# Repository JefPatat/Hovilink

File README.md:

# Hovilink
**Ho**mebrew **vi**essmann Opto**link** is a serial to network interface built to connect a Viessmann Vitotronic heating control to the network or internet.

# Motivation
I have been using a bulky self built interface based on information available openv together with PC software. This setup was not handy and serious overkill for the purpose. I want to enable myself to communicate with my heater over the network. To keep this flexible the harware is split up in an interface module which translates the optical signals to RS232. This RS232 can then be connected with various other interfaces.

# Limitations
The initial setup of this repository only aims to opensource my personal project and is limited to my personal heater and setup. I'm open to input of the community to expand on this.

# Hardware
The Vitotronic uses an optocoupler to communicate. It uses its status LEDs for this. The left, red, LED functions as an error indicator and at the same time as an infrared receiver. The right, green, LED as an operation indicator an infrared transmitter. Further details will be added to the wiki.

# Software
TBD

# Credits
https://openv.wikispaces.com

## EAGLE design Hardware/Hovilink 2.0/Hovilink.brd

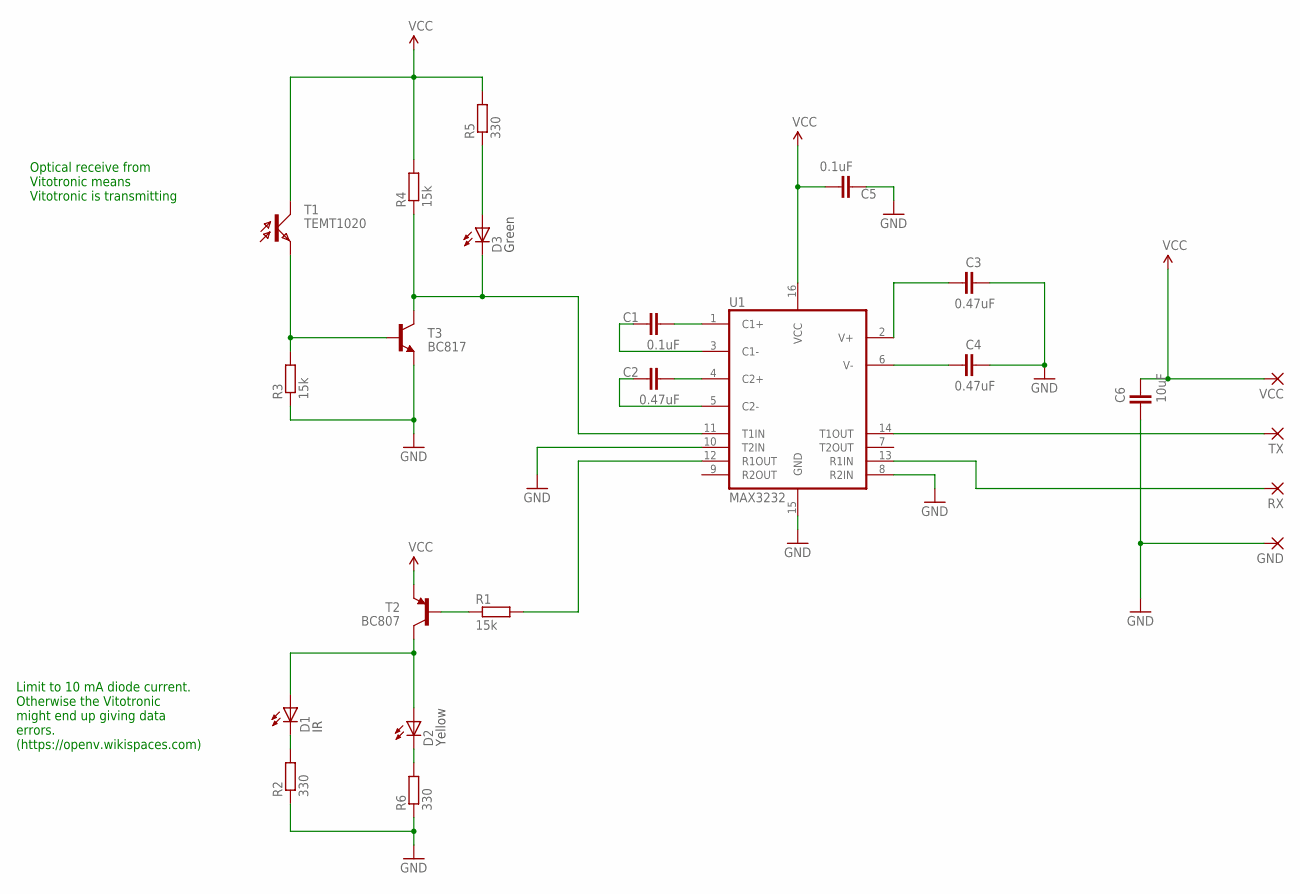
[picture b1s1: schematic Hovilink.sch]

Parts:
C1, C5: 0.1uF; 1206
C2, C3, C4: 0.47uF; 1206
C6: 10uF; 1206
D1: TSMF1020
D2: KP-2012SYCK; KNIGHTBRIGHT_2.0X1.25_SMD_LED
D3: KP-2012CGCK; KNIGHTBRIGHT_2.0X1.25_SMD_LED
GND: WIREPAD_2,54/1,3
R1, R3, R4: 15k; 1206
R2, R5, R6: 330; 1206
RX: WIREPAD_2,54/1,3
T1: TEMT1020
T2: BC807; SOT23_3
T3: BC817; SOT23_3
TX: WIREPAD_2,54/1,3
U1: MAX3232; SOIC16
VCC: WIREPAD_2,54/1,3

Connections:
GND: C3.2, C4.2, C5.1, C6.1, GND.1, R2.1, R3.1, R6.1, T3.2 (E), U1.8 (R2IN), U1.10 (T2IN), U1.15 (GND)
unnamed: C4.1, U1.6 (V-)
unnamed: C3.1, U1.2 (V+)
unnamed: R1.1, T2.1 (B)
unnamed: C1.2, U1.1 (C1+)
unnamed: C1.1, U1.3 (C1-)
unnamed: C2.2, U1.4 (C2+)
unnamed: C2.1, U1.5 (C2-)
unnamed: D1.P$1 (C), R2.2
unnamed: D1.P$2 (A), D2.P$1 (A), T2.3 (C)
unnamed: R1.2, U1.12 (R1OUT)
unnamed: TX.1, U1.14 (T1OUT)
unnamed: RX.1, U1.13 (R1IN)
unnamed: R3.2, T1.P$2 (E), T3.1 (B)
unnamed: D3.P$2 (C), R4.1, T3.3 (C), U1.11 (T1IN)
unnamed: D2.P$2 (C), R6.2
unnamed: D3.P$1 (A), R5.1
VCC: C5.2, C6.2, R4.2, R5.2, T1.P$1 (C), T2.2 (E), U1.16 (VCC), VCC.1

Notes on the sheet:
Optical receive from Vitotronic means Vitotronic is transmitting
Limit to 10 mA diode current. Otherwise the Vitotronic might end up giving data errors. (https://openv.wikispaces.com)

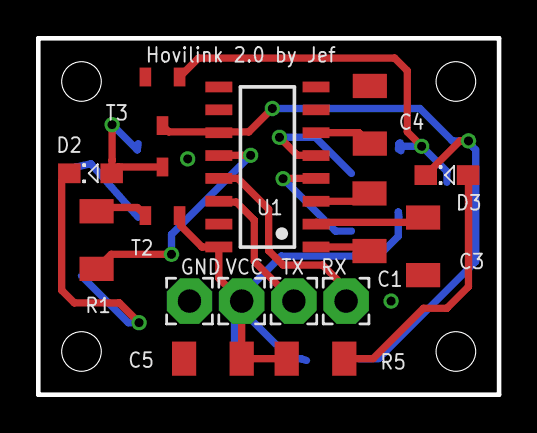
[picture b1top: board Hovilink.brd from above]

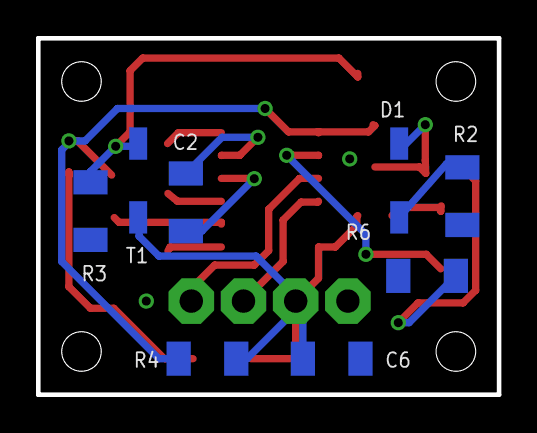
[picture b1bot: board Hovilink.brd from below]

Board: 2 copper layers, 25.6 x 19.8 mm, 23 parts (8 on the bottom side), 18 nets.

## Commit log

2017-10-23 Add Hovilink 2.0 schematic and board

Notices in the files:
parts and their libraries:
SparkFun-Aesthetics: Licensing: Creative Commons ShareAlike 4.0 International - https://creativecommons.org/licenses/by-sa/4.0
